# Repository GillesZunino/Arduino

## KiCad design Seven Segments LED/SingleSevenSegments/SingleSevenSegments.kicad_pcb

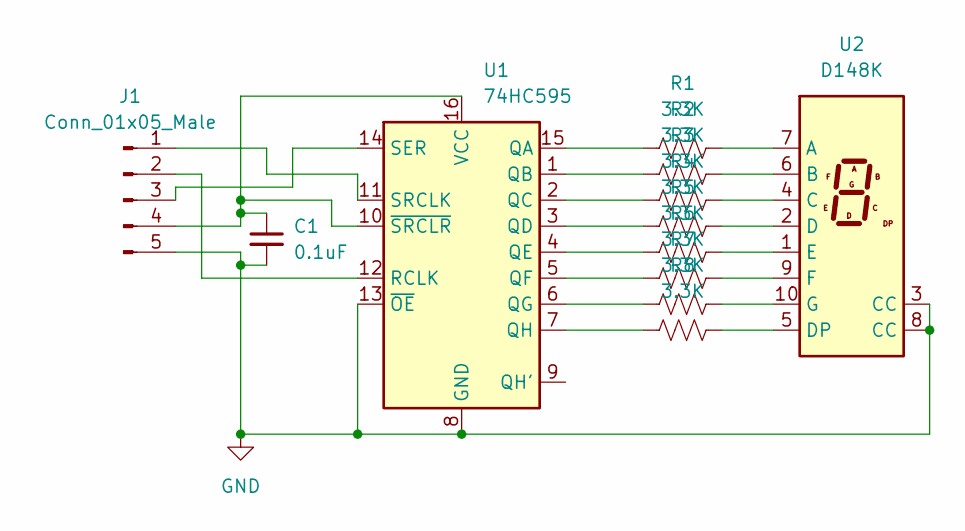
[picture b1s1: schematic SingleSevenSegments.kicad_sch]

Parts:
C1: 0.1uF; C_Disc_D5.0mm_W2.5mm_P2.50mm
J1: Conn_01x05_Male; PinHeader_1x05_P2.54mm_Vertical
R1, R2, R3, R4, R5, R6, R7, R8: 3.3K; R_Axial_DIN0411_L9.9mm_D3.6mm_P12.70mm_Horizontal
U1: 74HC595; DIP-16_W7.62mm
U2: D148K; 7SegmentLED_LTS6760_LTS6780

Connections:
GND: C1.2, J1.5, U1.8 (GND), U1.13 (~OE), U2.3 (CC), U2.8 (CC)
unnamed: C1.1, J1.4, U1.10 (~SRCLR), U1.16 (VCC)
unnamed: J1.1, U1.11 (SRCLK)
unnamed: J1.2, U1.12 (RCLK)
unnamed: J1.3, U1.14 (SER)
unnamed: R1.1, U2.7 (A)
unnamed: R1.2, U1.15 (QA)
unnamed: R2.1, U2.6 (B)
unnamed: R2.2, U1.1 (QB)
unnamed: R3.1, U2.4 (C)
unnamed: R3.2, U1.2 (QC)
unnamed: R4.1, U2.2 (D)
unnamed: R4.2, U1.3 (QD)
unnamed: R5.1, U2.1 (E)
unnamed: R5.2, U1.4 (QE)
unnamed: R6.1, U2.9 (F)
unnamed: R6.2, U1.5 (QF)
unnamed: R7.1, U2.10 (G)
unnamed: R7.2, U1.6 (QG)
unnamed: R8.1, U2.5 (DP)
unnamed: R8.2, U1.7 (QH)

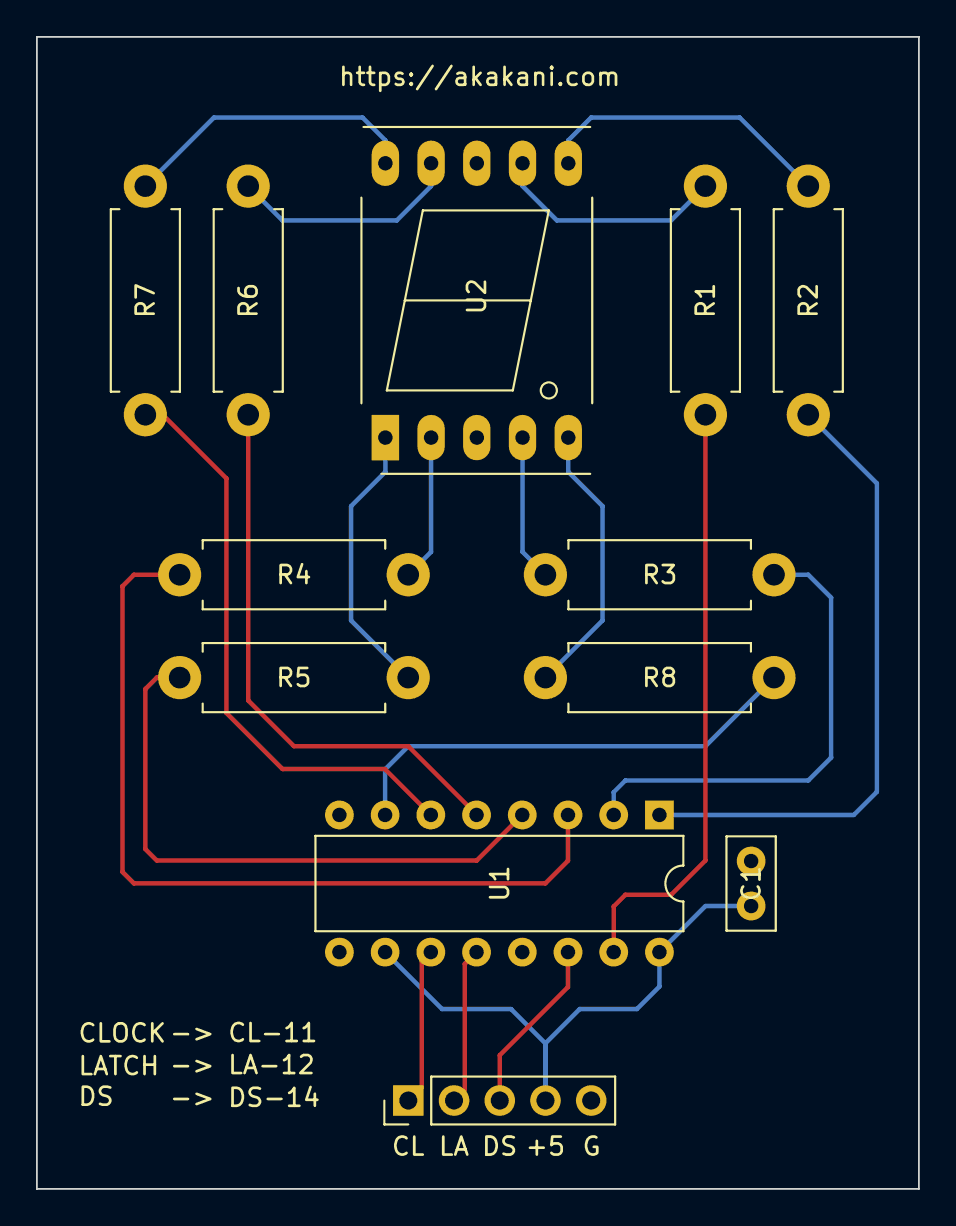
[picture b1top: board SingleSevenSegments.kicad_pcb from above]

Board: 2 copper layers, 49.0 x 64.0 mm, 12 parts (0 on the bottom side), 21 nets.

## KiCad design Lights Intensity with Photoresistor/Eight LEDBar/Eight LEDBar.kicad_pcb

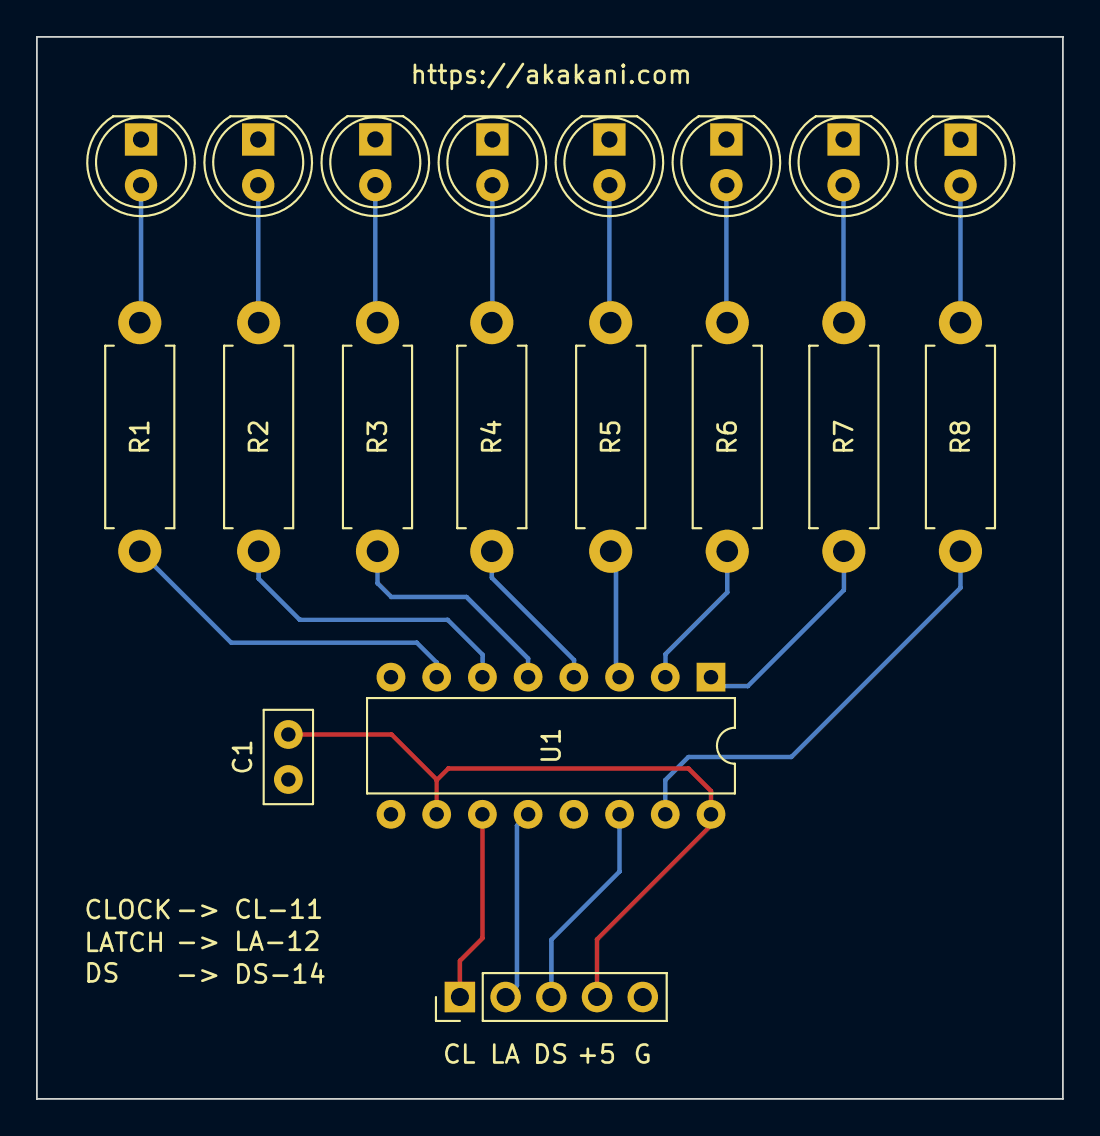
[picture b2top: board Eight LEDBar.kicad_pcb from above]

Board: 2 copper layers, 57.0 x 59.0 mm, 19 parts (0 on the bottom side), 21 nets.

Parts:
BLUE1, BLUE2: LED; LED_D5.0mm
C1: 0.1uF; C_Disc_D5.0mm_W2.5mm_P2.50mm
GREEN1, GREEN2: LED; LED_D5.0mm
J1: Conn_01x05_Male; PinHeader_1x05_P2.54mm_Vertical
R1, R2, R3, R4, R5, R6, R7, R8: R_US; R_Axial_DIN0411_L9.9mm_D3.6mm_P12.70mm_Horizontal
RED1, RED2: LED; LED_D5.0mm
U1: 74HC595; DIP-16_W7.62mm
YELOW1, YELOW2: LED; LED_D5.0mm

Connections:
GND: BLUE1.1 (K), BLUE2.1 (K), C1.2, GREEN1.1 (K), GREEN2.1 (K), J1.5, RED1.1 (K), RED2.1 (K), U1.8 (GND), U1.13 (~OE), YELOW1.1 (K), YELOW2.1 (K)
unnamed: BLUE1.2 (A), R1.2
unnamed: BLUE2.2 (A), R2.2
unnamed: C1.1, J1.4, U1.10 (~SRCLR), U1.16 (VCC)
unnamed: GREEN1.2 (A), R3.2
unnamed: GREEN2.2 (A), R4.2
unnamed: J1.1, U1.11 (SRCLK)
unnamed: J1.2, U1.12 (RCLK)
unnamed: J1.3, U1.14 (SER)
unnamed: R1.1, U1.7 (QH)
unnamed: R2.1, U1.6 (QG)
unnamed: R3.1, U1.5 (QF)
unnamed: R4.1, U1.4 (QE)
unnamed: R5.1, U1.3 (QD)
unnamed: R5.2, YELOW1.2 (A)
unnamed: R6.1, U1.2 (QC)
unnamed: R6.2, YELOW2.2 (A)
unnamed: R7.1, U1.1 (QB)
unnamed: R7.2, RED1.2 (A)
unnamed: R8.1, U1.15 (QA)
unnamed: R8.2, RED2.2 (A)

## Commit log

2021-09-20 Sketchto display temperature and humidity using a DHT11 on an SSD1351 128x128 OLED RGB display
2021-09-20 Waveshare 1.5in RGB OLED reference, sample code, data sheets
2021-10-04 Move Temperature and Humidity Project to Platform IO
2021-10-04 Configure for Platform IO debugging
2021-10-04 Disable GCC optimizations in debug build
2021-10-04 Combine common dependencies
2021-12-31 Add "Control DC motor via TIP120" - Make motor variable speed
2022-01-16 Add "Bi-Directional Control DC motor with LD293D" - Make motor variable speed - Make direction controllable via a push button
2022-01-31 [Control DC motor with LD293D] Add starting PWM calculation - When at 0, stop the moter - Above, clamp just below starting PWM
2022-02-22 Set builtin LED on during initialization and turn off when ready - Always start the motor turned off - Improve button debouncing
2022-02-22 Fix typo in comment
2022-02-22 Set builtin LED on during initialization and turn off when ready - Always start the motor turned off - Improve button debouncing - Describe how to see which direction is active
2022-02-22 Start with motor off
2022-03-05 [Control DC motor with Darlington Transitor] Express desired motor speed as ulong - Whitespace cleanup
2022-03-06 [Control DC motor with LD293D] Remove min PWM calculations - Clarify Left / Right pin digital pins
2022-03-06 [Control DC motor with LD293D] Fast stop motor between direction changes to be more gentle on mechanical parts
2022-05-08 Add "Lights Intensity with Photoresistor"
2022-05-08 Add KiCAD Project for "Lights Intensity with Photoresistor"
2022-05-08 Add Gerber and Dril files for "Lights Intensity with Photoresistor"
2022-05-08 Add "Seven Segments LED"
2022-05-08 Add KiCAD project for "Seven Segments LED"
2022-05-08 Add Gerber and Drill files for "Seven Segments LED"
2022-05-08 Add support for Mega2560, Nano, Nano Every to all projects - Add debugging capabilities
2022-05-08 [Lights Intensity with Photoresistor] Do not update LED bar display when the current reading is the same as the previous reading
2022-06-04 Add Ultrasnic Sensor with Air Temperature Correction
2022-06-04 Add Analog Joystick
2022-06-04 [Display Temperature And Humidity On OLED] Minor whitespace formatting
2022-06-13 Add Temperature - Humidity - LIght Intensity with 1602A LCD Display
2022-06-13 Add Real Time Clock with DS1307
2022-08-06 Configure clangtidy, cppcheck
2022-08-06 Add extensions.json
2022-08-06 Harmonize whitespaces within platformio.ini files
2022-08-06 Upgrade moononournation/GFX Library for Arduino (1.1.5 -> 1.2.6), robtillaart/DHTStable (1.0.1 -> 1.1.1)
2022-08-06 Upgrade adafruit/RTClib (2.0.2 -> 2.0.3)
2022-08-07 Harmonize C and C++ versions between compiler and static analysis (gcc: -std=gnu11 -std=gnu++17, cppcheck: --std=c11 --std=c++17)
2022-12-12 Add "Rotaty Encoder"
2022-12-12 [Rotary Encoder] Do not use String - This reduce the code size down by aobut 10K
2022-12-12 Add "Servo Motor" - Simple servo motor control with position taken from a rotary encoder
2022-12-12 [Rotary Encoder] Correctly acquire the servo values under mutual exclusion
2022-12-12 [Rotary Encoder] Organize code to make it easier to factor into its own seprate class / file - Unify programming model between polling and interrupt based implementations
2022-12-12 [Rotary Encoder] Extract rotary encoder handlinh code into its own file - Update main program to use the extracted code
2022-12-17 [Rotary Encoder] Centralize reusable classes into Personal-Libraries
2022-12-17 Centralize "Eight LED Bar" and "Single Seven Segment" libraries under 'Personal-Libraries'
2022-12-20 [Servo] Use common RotaryEncoder library
2022-12-23 Add MAX7219 library
2022-12-23 Add "LED 8x8 Matrix" project to control a 8x8 LED matrix via a MAX7219
2022-12-23 [Seven Segements LED] Use 'avr8-stubs-utilities.h' from Personal Libraries - Remove local copy - Move digital pins to higher numbers for ease of connection - Upgrade PlatformIO configuration
2022-12-23 Add Personal Library 'Debugger\avr8-stubs-utilities.h'
2022-12-23 Add "Gyroscope - Accelerometer with MPU6050'
2022-12-23 Add 'Movement Detection with PIR'
2022-12-26 Serial.begin(9600) -> Serial.begin(115200)
2022-12-26 Add "RFID with MRFC522"
2022-12-26 Upgrade moononournation/GFX Library for Arduino (1.2.6->1.3.1) and adafruit/RTClib (2.0.3->2.1.1)
2022-12-26 Unify platformio.ini files - Remove teensy configuration if it existed - Combine libraries under [env:lib_deps] -Set monitor_speed to 115200
2022-12-27 Add 'WS2815 Driver' for single addressable LED strips
2022-12-30 [Seven Segment LED] Add '-' to the list of supported characters
2022-12-30 [Seven Segment LED] Add depiction of seven segment segment letters
2023-01-28 Add personal library 'Eight Seven Segments Displays'
2023-01-28 Add "Eight Seven Segment Display With MAX7219"
2023-04-02 [Seven Segment LED] Formalize the number of digits as a constant - DO not hardcode "8" or "7" - Fix "clearDisplay()"
2023-04-02 [Seven Segment With MAX7219] Do not hardcode number of digits and use library constants instead - Reduce brightness of display
